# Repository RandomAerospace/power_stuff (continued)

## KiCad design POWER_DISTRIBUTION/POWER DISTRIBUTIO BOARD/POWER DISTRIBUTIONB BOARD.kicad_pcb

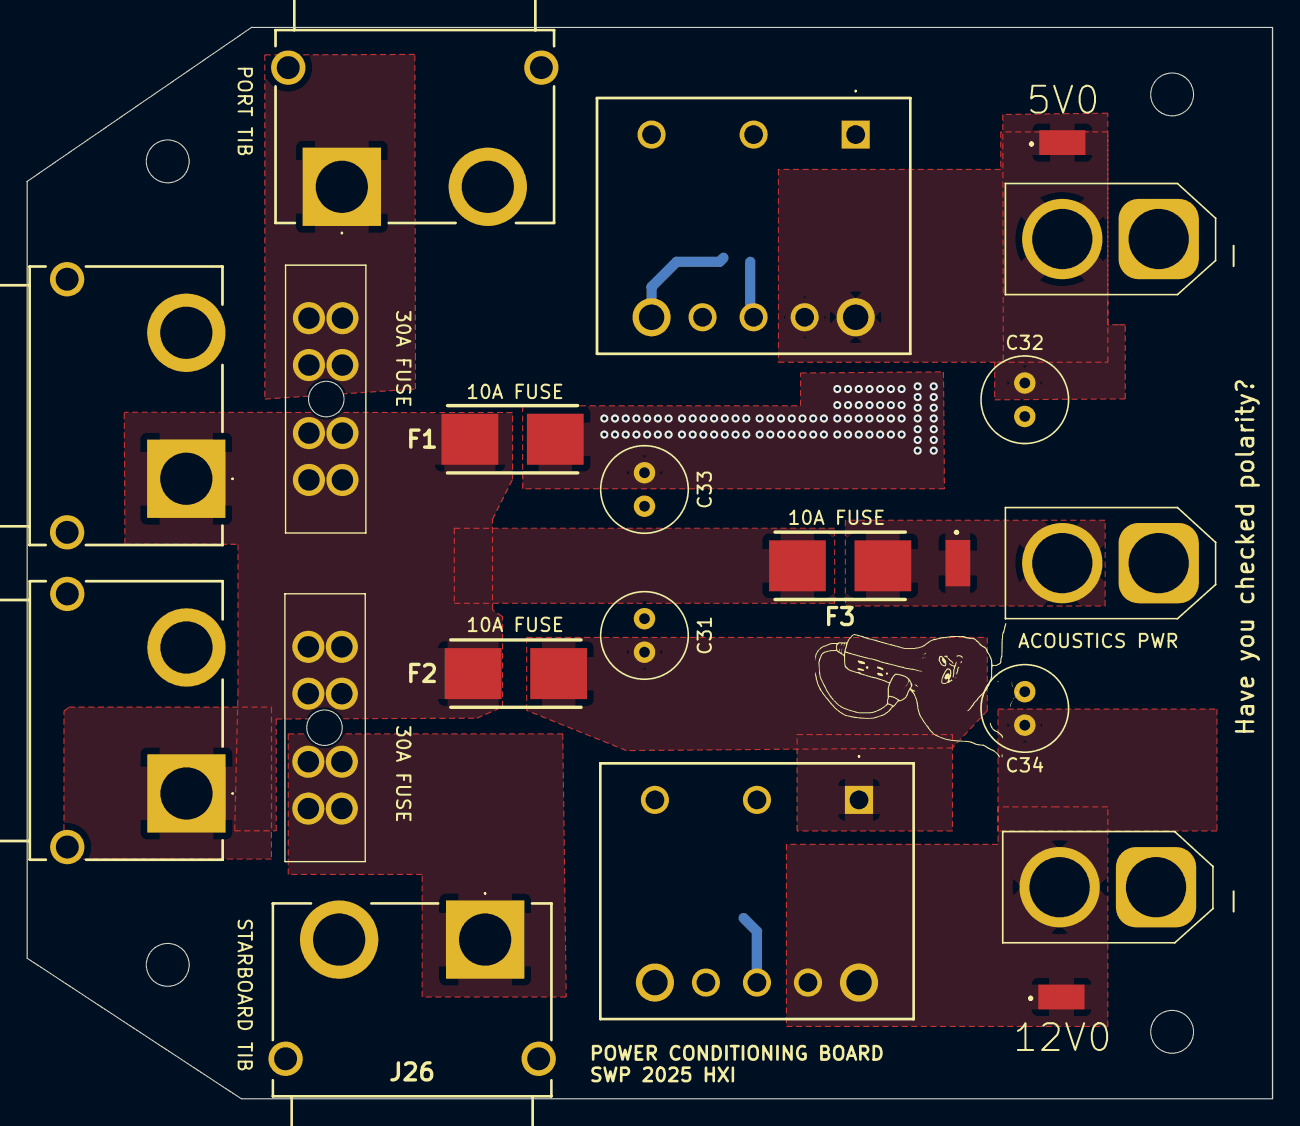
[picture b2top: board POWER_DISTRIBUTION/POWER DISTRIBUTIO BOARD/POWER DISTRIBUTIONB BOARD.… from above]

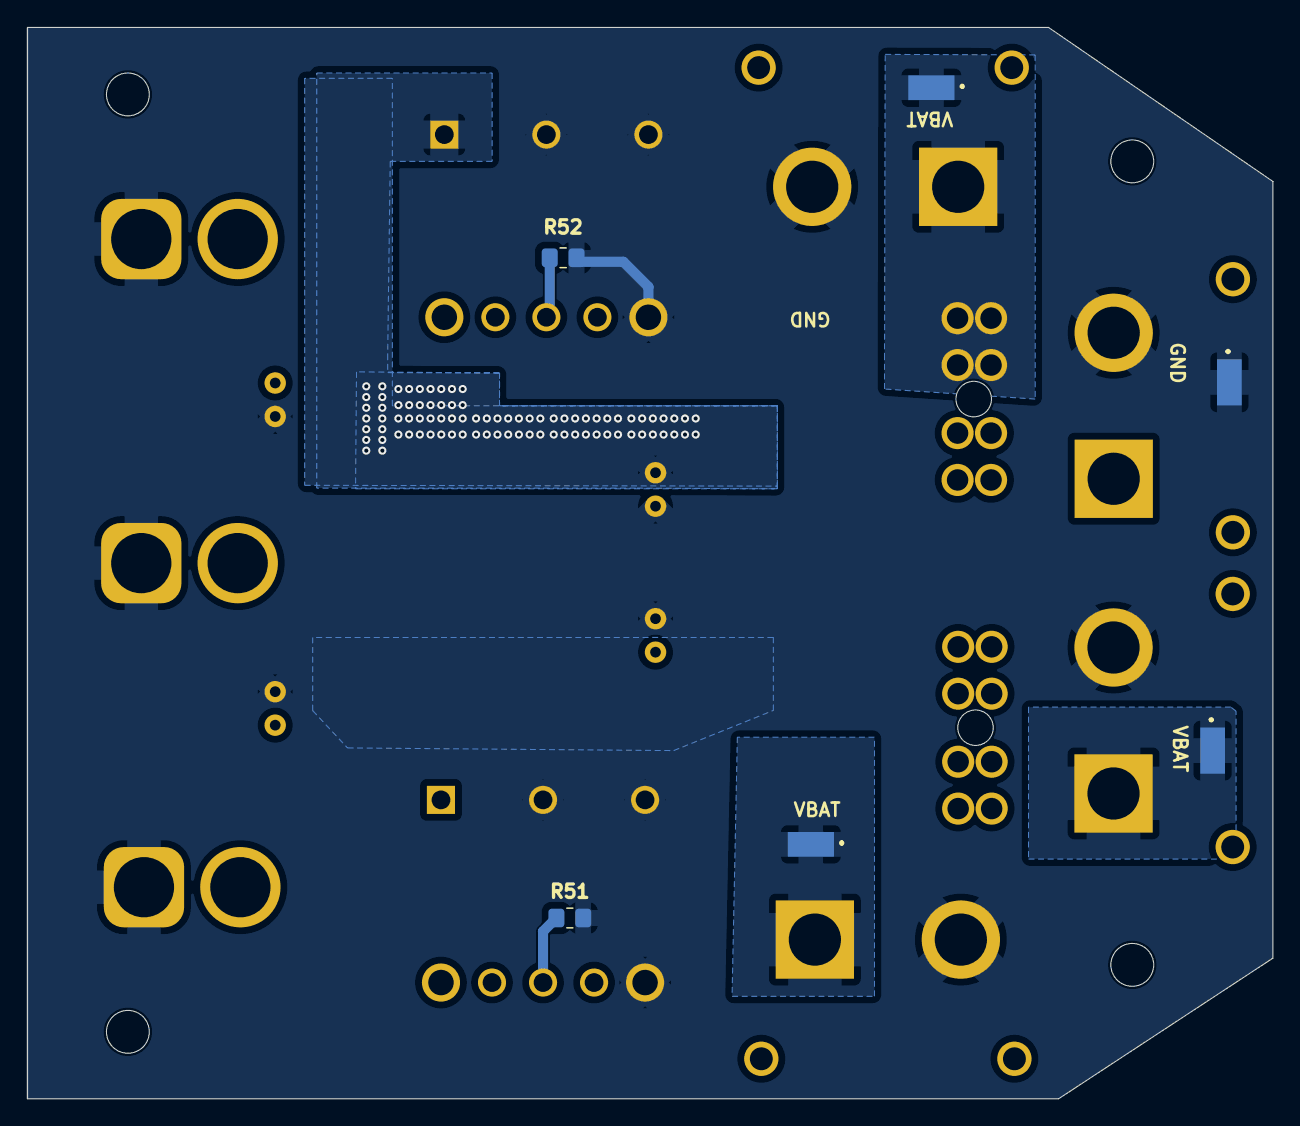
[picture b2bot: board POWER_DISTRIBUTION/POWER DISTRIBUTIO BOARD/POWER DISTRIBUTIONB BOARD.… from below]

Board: 2 copper layers, 93.0 x 80.0 mm, 31 parts (6 on the bottom side), 9 nets.

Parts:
C31, C32, C33, C34: 47u; C_Radial_D6.3mm_H5.0mm_P2.50mm
F1, F2, F3: 0154010.DR; 0154001.DRT
H1, H2, H3, H4: MountingHole; MountingHole_3.2mm_M3_ISO7380
J1, J4, J7: Conn_01x02_Socket; AMASS_XT60-F_1x02_P7.20mm_Vertical
J25, J26, J27, J28: XT90PW-F; XT90PWF
PS3, PS4: RPMA5.0-8.0_OF; RPMA5080OF
R51: 1k82; R_0805_2012Metric_Pad1.20x1.40mm_HandSolder
R52: 8k66; R_0805_2012Metric_Pad1.20x1.40mm_HandSolder
TP3, TP4, TP5, TP6, TP7, TP8, TP24: S1751-46R; S175146R
U2, U3: 178.6165.0002; 17861650002

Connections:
+5V: C32.1, J7.2, PS4.7 (+SENSE), PS4.8 (+VOUT), TP5.1
+12V: C34.1, J1.2, PS3.7 (+SENSE), PS3.8 (+VOUT), TP3.1
GND: C31.2, C32.2, C33.2, C34.2, J1.1, J4.1, J7.1, J25.2 (-), J26.2 (-), J27.2 (-), J28.2 (-), PS3.2 (CTRL), PS3.3 (-VIN), PS3.4 (-VOUT), PS4.2 (CTRL), PS4.3 (-VIN), PS4.4 (-VOUT), R51.2, R52.2, TP7.1
unnamed: PS3.6 (TRIM), R51.1
unnamed: PS4.6 (TRIM), R52.1
VBAT+: C31.1, C33.1, F1.1, F1.2, F2.1, F2.2, F3.1, J27.1 (+), J28.1 (+), PS3.1 (+VIN), PS4.1 (+VIN), TP6.1, U2.5, U2.6, U2.7, U2.8, U3.5, U3.6, U3.7, U3.8
VBAT_A_FUSED: F3.2, J4.2, TP4.1
VBAT_FUSED: J26.1 (+), TP8.1, U3.1, U3.2, U3.3, U3.4
VBAT_P_FUSED: J25.1 (+), TP24.1, U2.1, U2.2, U2.3, U2.4

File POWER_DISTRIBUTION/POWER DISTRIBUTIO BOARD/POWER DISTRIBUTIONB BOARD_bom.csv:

"Id";"Designator";"Footprint";"Quantity";"Designation";"Supplier and ref";
1;"TP4,TP5,TP3,TP6,TP8,TP24,TP7";"S175146R";7;"S1751-46R";;;
2;"F2,F1,F3";"0154001.DRT";3;"0154010.DR";;;
3;"C31,C34,C33,C32";"C_Radial_D6.3mm_H5.0mm_P2.50mm";4;"47u";;;
4;"J25,J26,J28,J27";"XT90PWF";4;"XT90PW-F";;;
5;"J7,J4,J1";"AMASS_XT60-F_1x02_P7.20mm_Vertical";3;"Conn_01x02_Socket";;;
6;"PS3,PS4";"RPMA5080OF";2;"RPMA5.0-8.0_OF";;;
7;"U3,U2";"17861650002";2;"178.6165.0002";;;
8;"R52";"R_0805_2012Metric_Pad1.20x1.40mm_HandSolder";1;"8k66";;;
9;"R51";"R_0805_2012Metric_Pad1.20x1.40mm_HandSolder";1;"1k82";;;

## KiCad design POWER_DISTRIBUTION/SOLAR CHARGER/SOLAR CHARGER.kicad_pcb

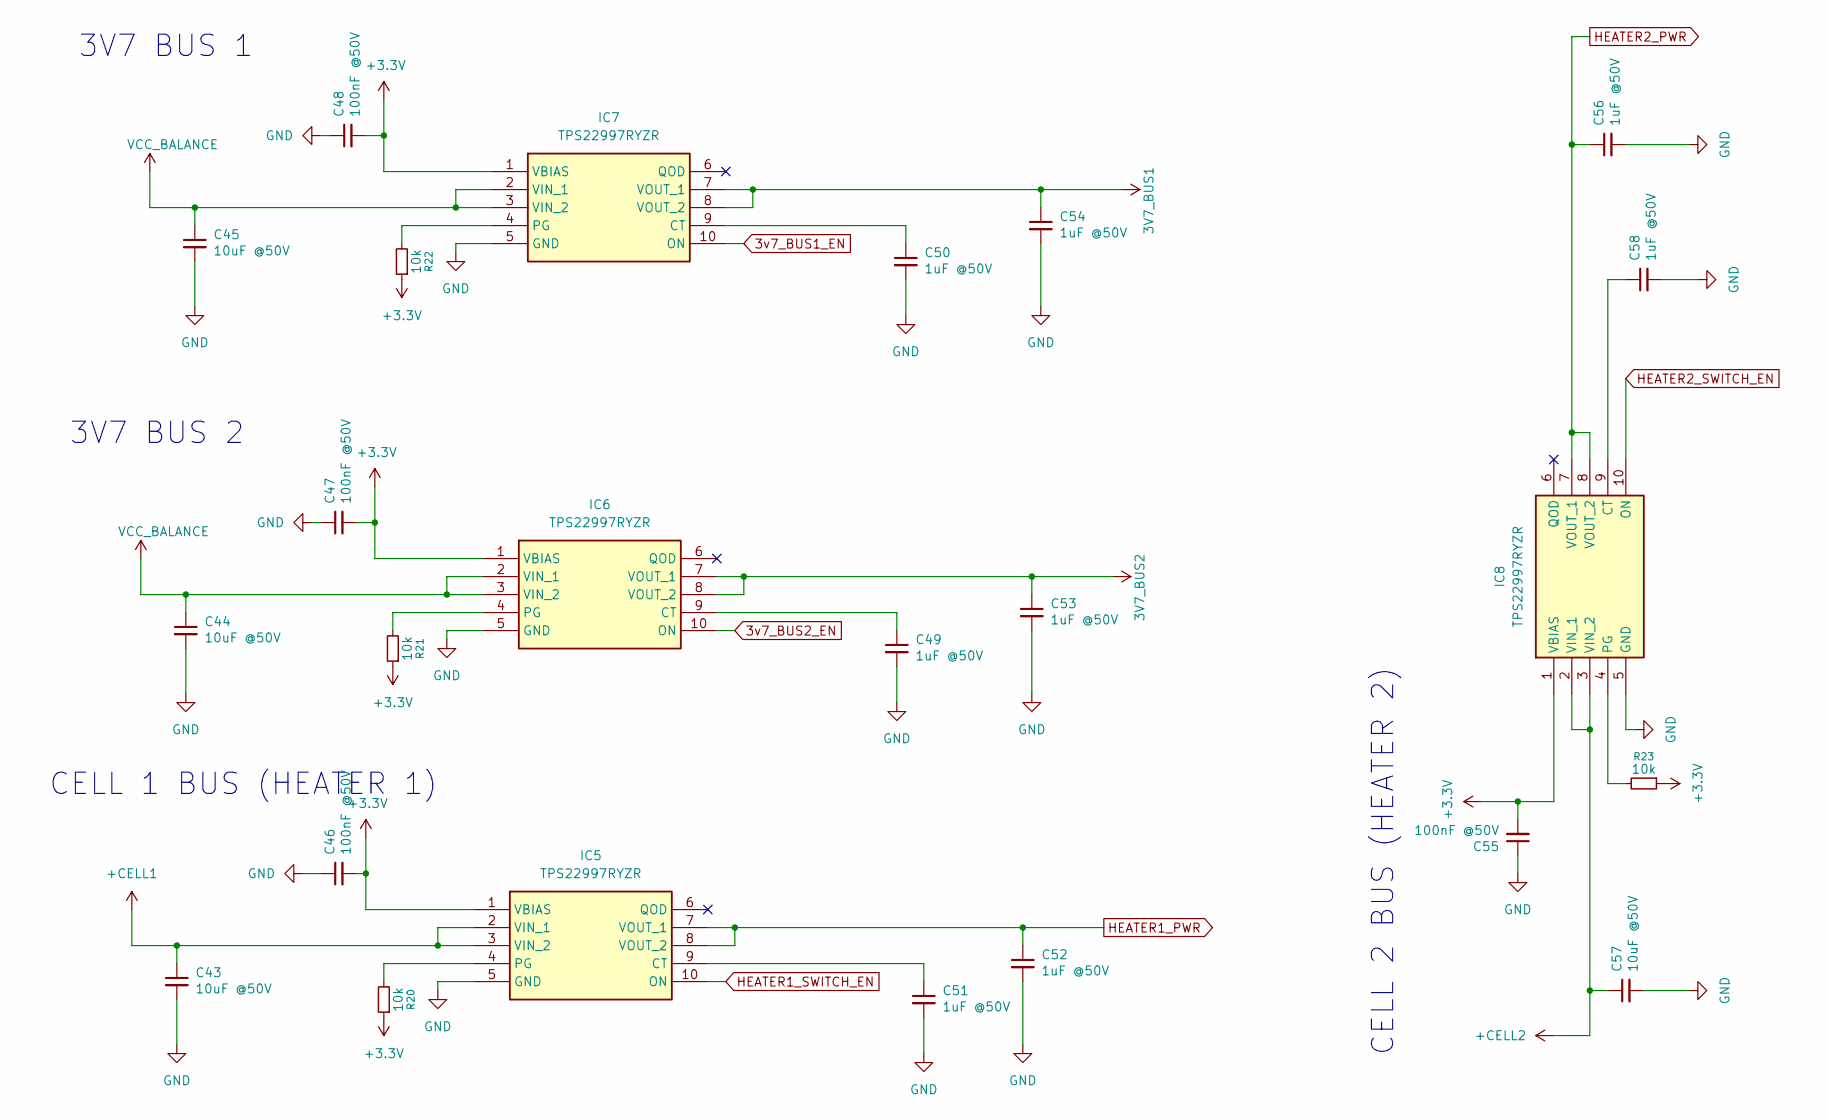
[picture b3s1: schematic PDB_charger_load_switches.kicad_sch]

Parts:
C43, C44, C45, C57: 10uF @50V; C_1210_3225Metric_Pad1.33x2.70mm_HandSolder
C46, C47, C48, C55: 100nF @50V; C_0402_1005Metric_Pad0.74x0.62mm_HandSolder
C49, C50, C51, C52, C53, C54, C56, C58: 1uF @50V; C_0805_2012Metric_Pad1.18x1.45mm_HandSolder
IC5, IC6, IC7, IC8: TPS22997RYZR; Mouser Part Number 595-TPS22997RYZR
R20, R21, R22, R23: 10k; R_0402_1005Metric_Pad0.72x0.64mm_HandSolder

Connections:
3V7_BUS1: C54.1, IC7.7 (VOUT_1), IC7.8 (VOUT_2); also elsewhere on the board
3V7_BUS2: C53.1, IC6.7 (VOUT_1), IC6.8 (VOUT_2); also elsewhere on the board
3v7_BUS1_EN: IC7.10 (ON); also elsewhere on the board
3v7_BUS2_EN: IC6.10 (ON); also elsewhere on the board
+3.3V: C46.2, C47.2, C48.2, C55.2, IC5.1 (VBIAS), IC6.1 (VBIAS), IC7.1 (VBIAS), IC8.1 (VBIAS), R20.1, R21.1, R22.1, R23.1; also elsewhere on the board
+CELL1: C43.1, IC5.2 (VIN_1), IC5.3 (VIN_2); also elsewhere on the board
+CELL2: C57.1, IC8.2 (VIN_1), IC8.3 (VIN_2); also elsewhere on the board
GND: C43.2, C44.2, C45.2, C46.1, C47.1, C48.1, C49.2, C50.2, C51.2, C52.2, C53.2, C54.2, C55.1, C56.2, C57.2, C58.2, IC5.5 (GND), IC6.5 (GND), IC7.5 (GND), IC8.5 (GND); also elsewhere on the board
HEATER1_PWR: C52.1, IC5.7 (VOUT_1), IC5.8 (VOUT_2); also elsewhere on the board
HEATER1_SWITCH_EN: IC5.10 (ON); also elsewhere on the board
HEATER2_PWR: C56.1, IC8.7 (VOUT_1), IC8.8 (VOUT_2); also elsewhere on the board
HEATER2_SWITCH_EN: IC8.10 (ON); also elsewhere on the board
unnamed: C51.1, IC5.9 (CT)
unnamed: IC5.4 (PG), R20.2
unnamed: C49.1, IC6.9 (CT)
unnamed: IC6.4 (PG), R21.2
unnamed: C50.1, IC7.9 (CT)
unnamed: IC7.4 (PG), R22.2
unnamed: C58.1, IC8.9 (CT)
unnamed: IC8.4 (PG), R23.2
VCC_BALANCE: C44.1, C45.1, IC6.2 (VIN_1), IC6.3 (VIN_2), IC7.2 (VIN_1), IC7.3 (VIN_2); also elsewhere on the board

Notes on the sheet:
3V7 BUS 2
CELL 2 BUS (HEATER 2)
CELL 1 BUS (HEATER 1)
3V7 BUS 1

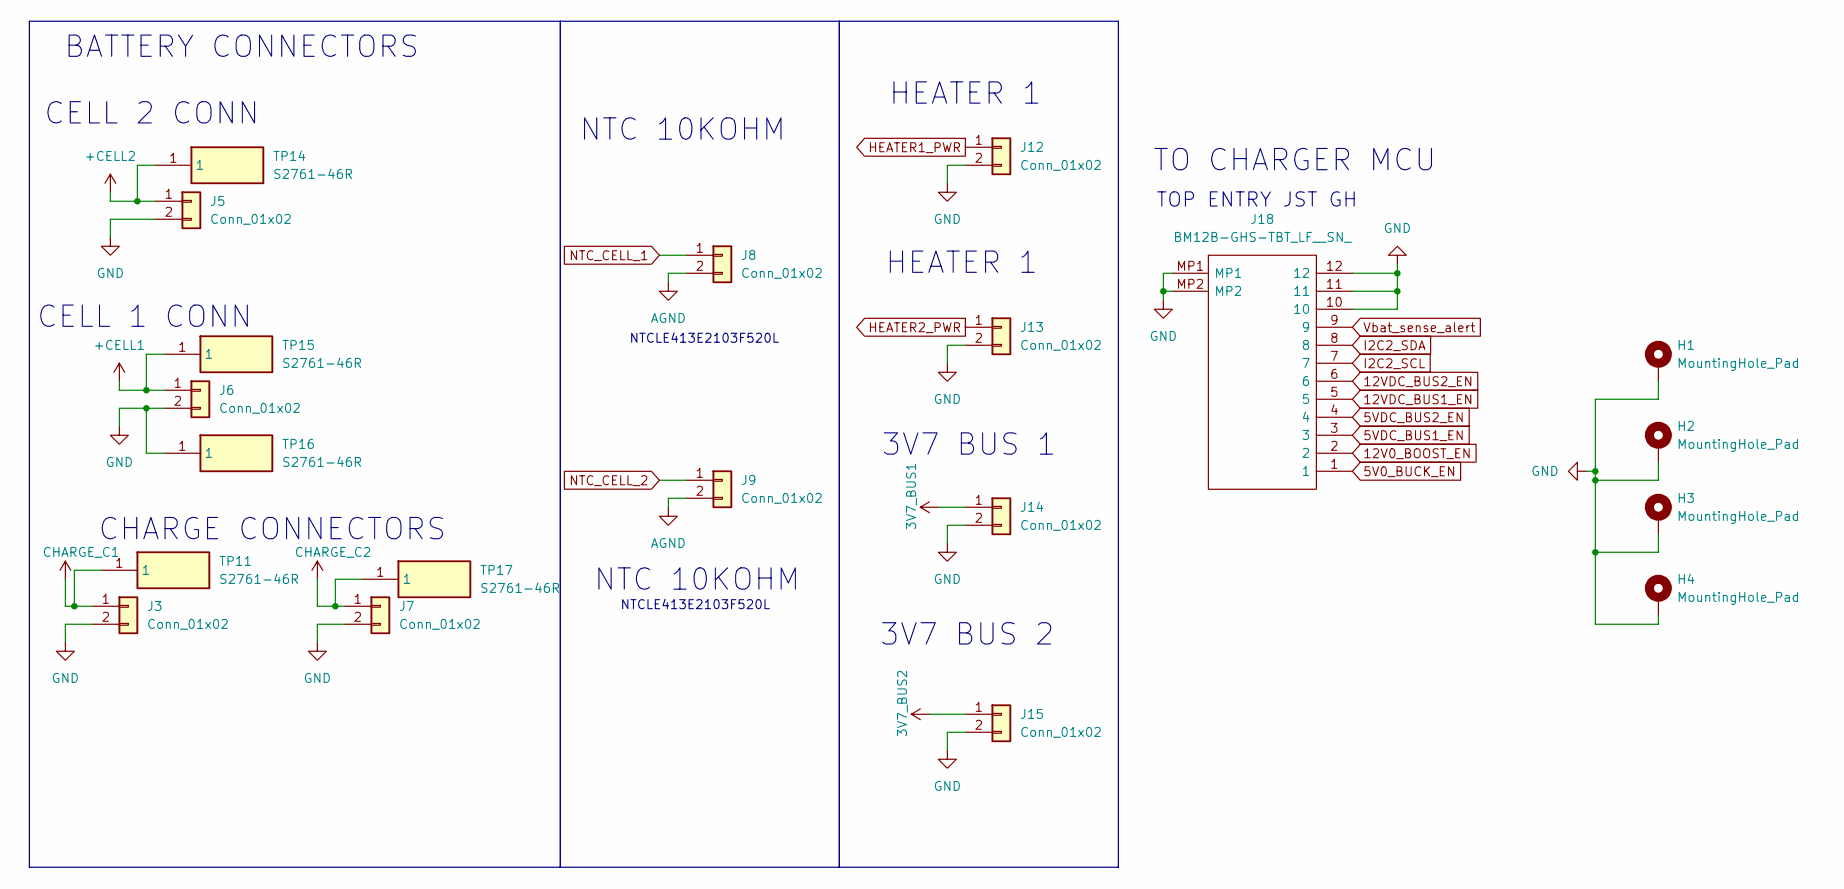
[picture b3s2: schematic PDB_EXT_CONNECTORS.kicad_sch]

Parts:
H1, H2, H3, H4: MountingHole_Pad; MountingHole_3.2mm_M3_Pad_Via
J3, J5, J6, J7: Conn_01x02; JST_PH_S2B-PH-K_1x02_P2.00mm_Horizontal
J8, J9: Conn_01x02; SolderWire-0.127sqmm_1x02_P3.7mm_D0.48mm_OD1mm
J12, J13, J14, J15: Conn_01x02; JST_PH_B2B-PH-K_1x02_P2.00mm_Vertical
J18: BM12B-GHS-TBT_LF__SN_; BM12BGHSTBTLFSN; Mouser Part Number 306-BM12BGHSTBTLFSNN
TP11, TP14, TP15, TP16, TP17: S2761-46R; S276146R; Mouser Part Number 855-S2761-46R

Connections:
3V7_BUS1: J14.1; also elsewhere on the board
3V7_BUS2: J15.1; also elsewhere on the board
5V0_BUCK_EN: J18.1; also elsewhere on the board
5VDC_BUS1_EN: J18.3; also elsewhere on the board
5VDC_BUS2_EN: J18.4; also elsewhere on the board
12V0_BOOST_EN: J18.2; also elsewhere on the board
12VDC_BUS1_EN: J18.5; also elsewhere on the board
12VDC_BUS2_EN: J18.6; also elsewhere on the board
+CELL1: J6.1, TP15.1; also elsewhere on the board
+CELL2: J5.1, TP14.1; also elsewhere on the board
AGND: J8.2, J9.2
CHARGE_C1: J3.1, TP11.1; also elsewhere on the board
CHARGE_C2: J7.1, TP17.1; also elsewhere on the board
GND: H1.1, H2.1, H3.1, H4.1, J3.2, J5.2, J6.2, J7.2, J12.2, J13.2, J14.2, J15.2, J18.10, J18.11, J18.12, J18.MP1, J18.MP2, TP16.1; also elsewhere on the board
HEATER1_PWR: J12.1; also elsewhere on the board
HEATER2_PWR: J13.1; also elsewhere on the board
I2C2_SCL: J18.7; also elsewhere on the board
I2C2_SDA: J18.8; also elsewhere on the board
NTC_CELL_1: J8.1; also elsewhere on the board
NTC_CELL_2: J9.1; also elsewhere on the board
Vbat_sense_alert: J18.9; also elsewhere on the board

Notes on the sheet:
TO CHARGER MCU
HEATER 1
TOP ENTRY JST GH
CELL 2 CONN
3V7 BUS 1
NTC 10KOHM
NTCLE413E2103F520L
CELL 1 CONN
BATTERY CONNECTORS
3V7 BUS 2
CHARGE CONNECTORS

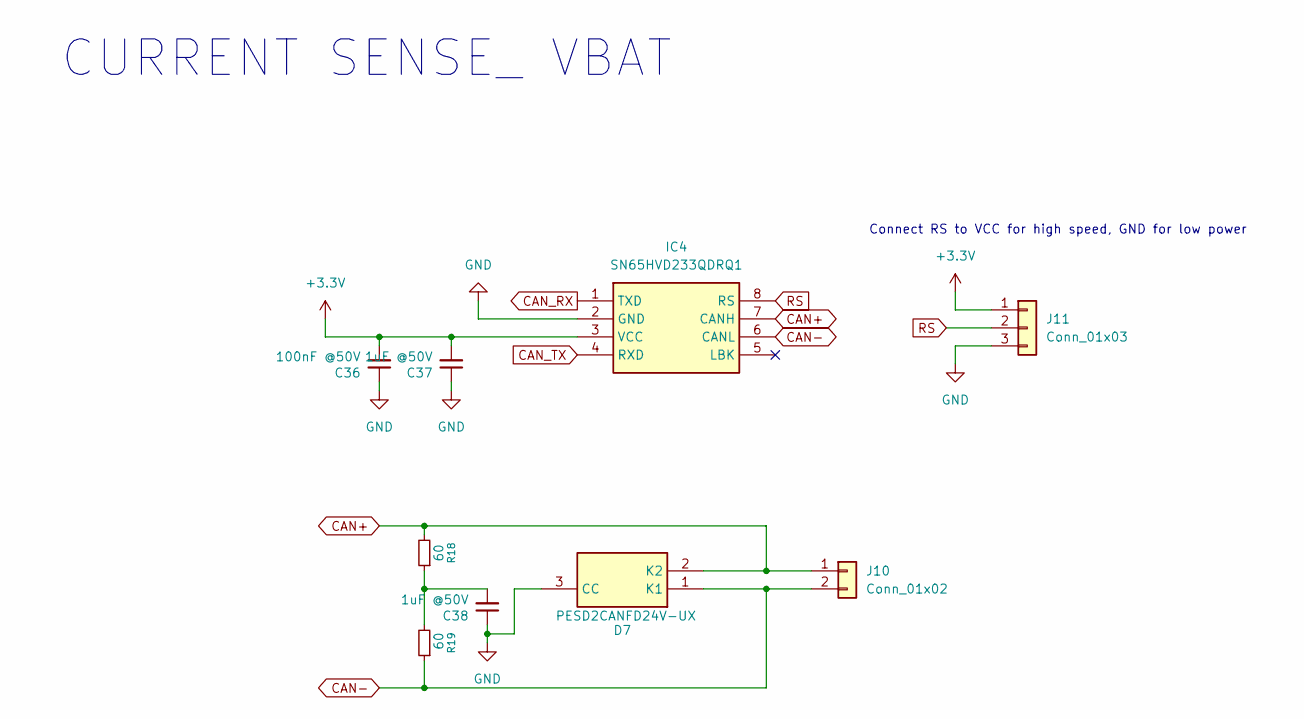
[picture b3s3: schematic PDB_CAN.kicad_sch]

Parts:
C36: 100nF @50V; C_0402_1005Metric_Pad0.74x0.62mm_HandSolder
C37, C38: 1uF @50V; C_0805_2012Metric_Pad1.18x1.45mm_HandSolder
D7: PESD2CANFD24V-UX; SOT65P210X110-3N; Mouser Part Number 771-PESD2CANFD24V-UX
IC4: SN65HVD233QDRQ1; SOIC127P600X175-8N; Mouser Part Number 595-SN65HVD233QDRQ1
J10: Conn_01x02; JST_PH_B2B-PH-K_1x02_P2.00mm_Vertical
J11: Conn_01x03; PinHeader_1x03_P2.54mm_Vertical
R18, R19: 60; R_0603_1608Metric

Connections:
+3.3V: C36.2, C37.2, IC4.3 (VCC), J11.1; also elsewhere on the board
CAN+: D7.2 (K2), IC4.7 (CANH), J10.1, R18.2
CAN-: D7.1 (K1), IC4.6 (CANL), J10.2, R19.1
CAN_RX: IC4.1 (TXD); also elsewhere on the board
CAN_TX: IC4.4 (RXD); also elsewhere on the board
GND: C36.1, C37.1, C38.1, D7.3 (CC), IC4.2 (GND), J11.3; also elsewhere on the board
unnamed: C38.2, R18.1, R19.2
RS: IC4.8 (RS), J11.2

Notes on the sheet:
Connect RS to VCC for high speed, GND for low power
CURRENT SENSE_ VBAT

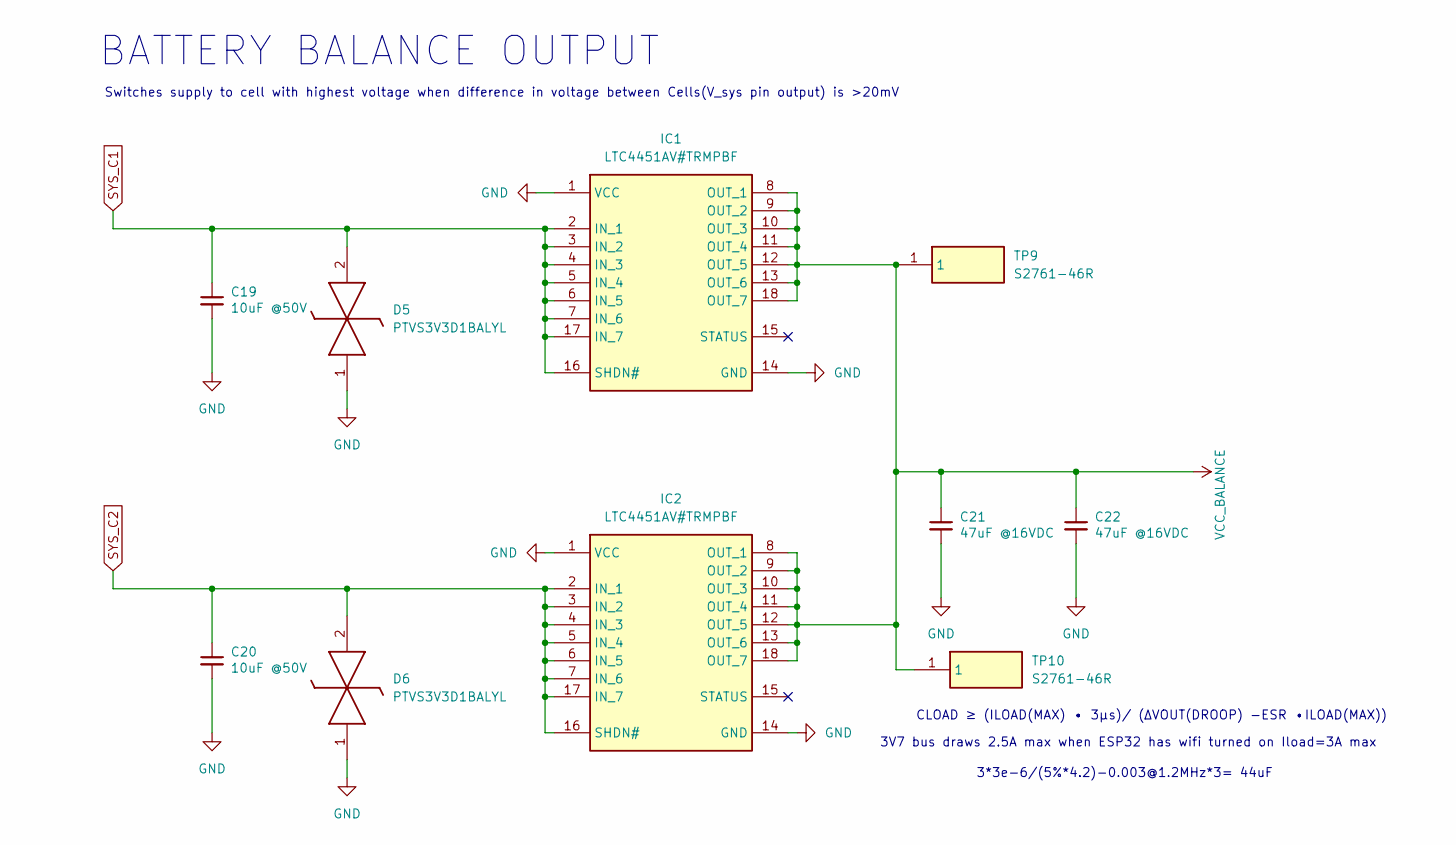
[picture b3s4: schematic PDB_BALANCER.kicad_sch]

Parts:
C19, C20: 10uF @50V; C_1210_3225Metric_Pad1.33x2.70mm_HandSolder
C21, C22: 47uF @16VDC; C_1206_3216Metric_Pad1.33x1.80mm_HandSolder
D5, D6: PTVS3V3D1BALYL; PESD5V0S1BL315; Mouser Part Number 771-PTVS3V3D1BALYL
IC1, IC2: LTC4451AV#TRMPBF; LTC4451AVTRMPBF; Mouser Part Number 584-LTC4451AVTRMPBF
TP9, TP10: S2761-46R; S276146R; Mouser Part Number 855-S2761-46R

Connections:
GND: C19.2, C20.2, C21.2, C22.2, D5.1 (K1), D6.1 (K1), IC1.1 (VCC), IC1.14 (GND), IC2.1 (VCC), IC2.14 (GND); also elsewhere on the board
SYS_C1: C19.1, D5.2 (K2), IC1.2 (IN_1), IC1.3 (IN_2), IC1.4 (IN_3), IC1.5 (IN_4), IC1.6 (IN_5), IC1.7 (IN_6), IC1.16 (SHDN#), IC1.17 (IN_7); also elsewhere on the board
SYS_C2: C20.1, D6.2 (K2), IC2.2 (IN_1), IC2.3 (IN_2), IC2.4 (IN_3), IC2.5 (IN_4), IC2.6 (IN_5), IC2.7 (IN_6), IC2.16 (SHDN#), IC2.17 (IN_7); also elsewhere on the board
VCC_BALANCE: C21.1, C22.1, IC1.8 (OUT_1), IC1.9 (OUT_2), IC1.10 (OUT_3), IC1.11 (OUT_4), IC1.12 (OUT_5), IC1.13 (OUT_6), IC1.18 (OUT_7), IC2.8 (OUT_1), IC2.9 (OUT_2), IC2.10 (OUT_3), IC2.11 (OUT_4), IC2.12 (OUT_5), IC2.13 (OUT_6), IC2.18 (OUT_7), TP9.1, TP10.1; also elsewhere on the board

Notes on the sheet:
BATTERY BALANCE OUTPUT
3*3e-6/(5%*4.2)-0.003@1.2MHz*3= 44uF
Switches supply to cell with highest voltage when difference in voltage between Cells(V_sys pin output) is >20mV
3V7 bus draws 2.5A max when ESP32 has wifi turned on Iload=3A max
CLOAD ≥ (ILOAD(MAX) • 3μs)/ (ΔVOUT(DROOP) -ESR •ILOAD(MAX))

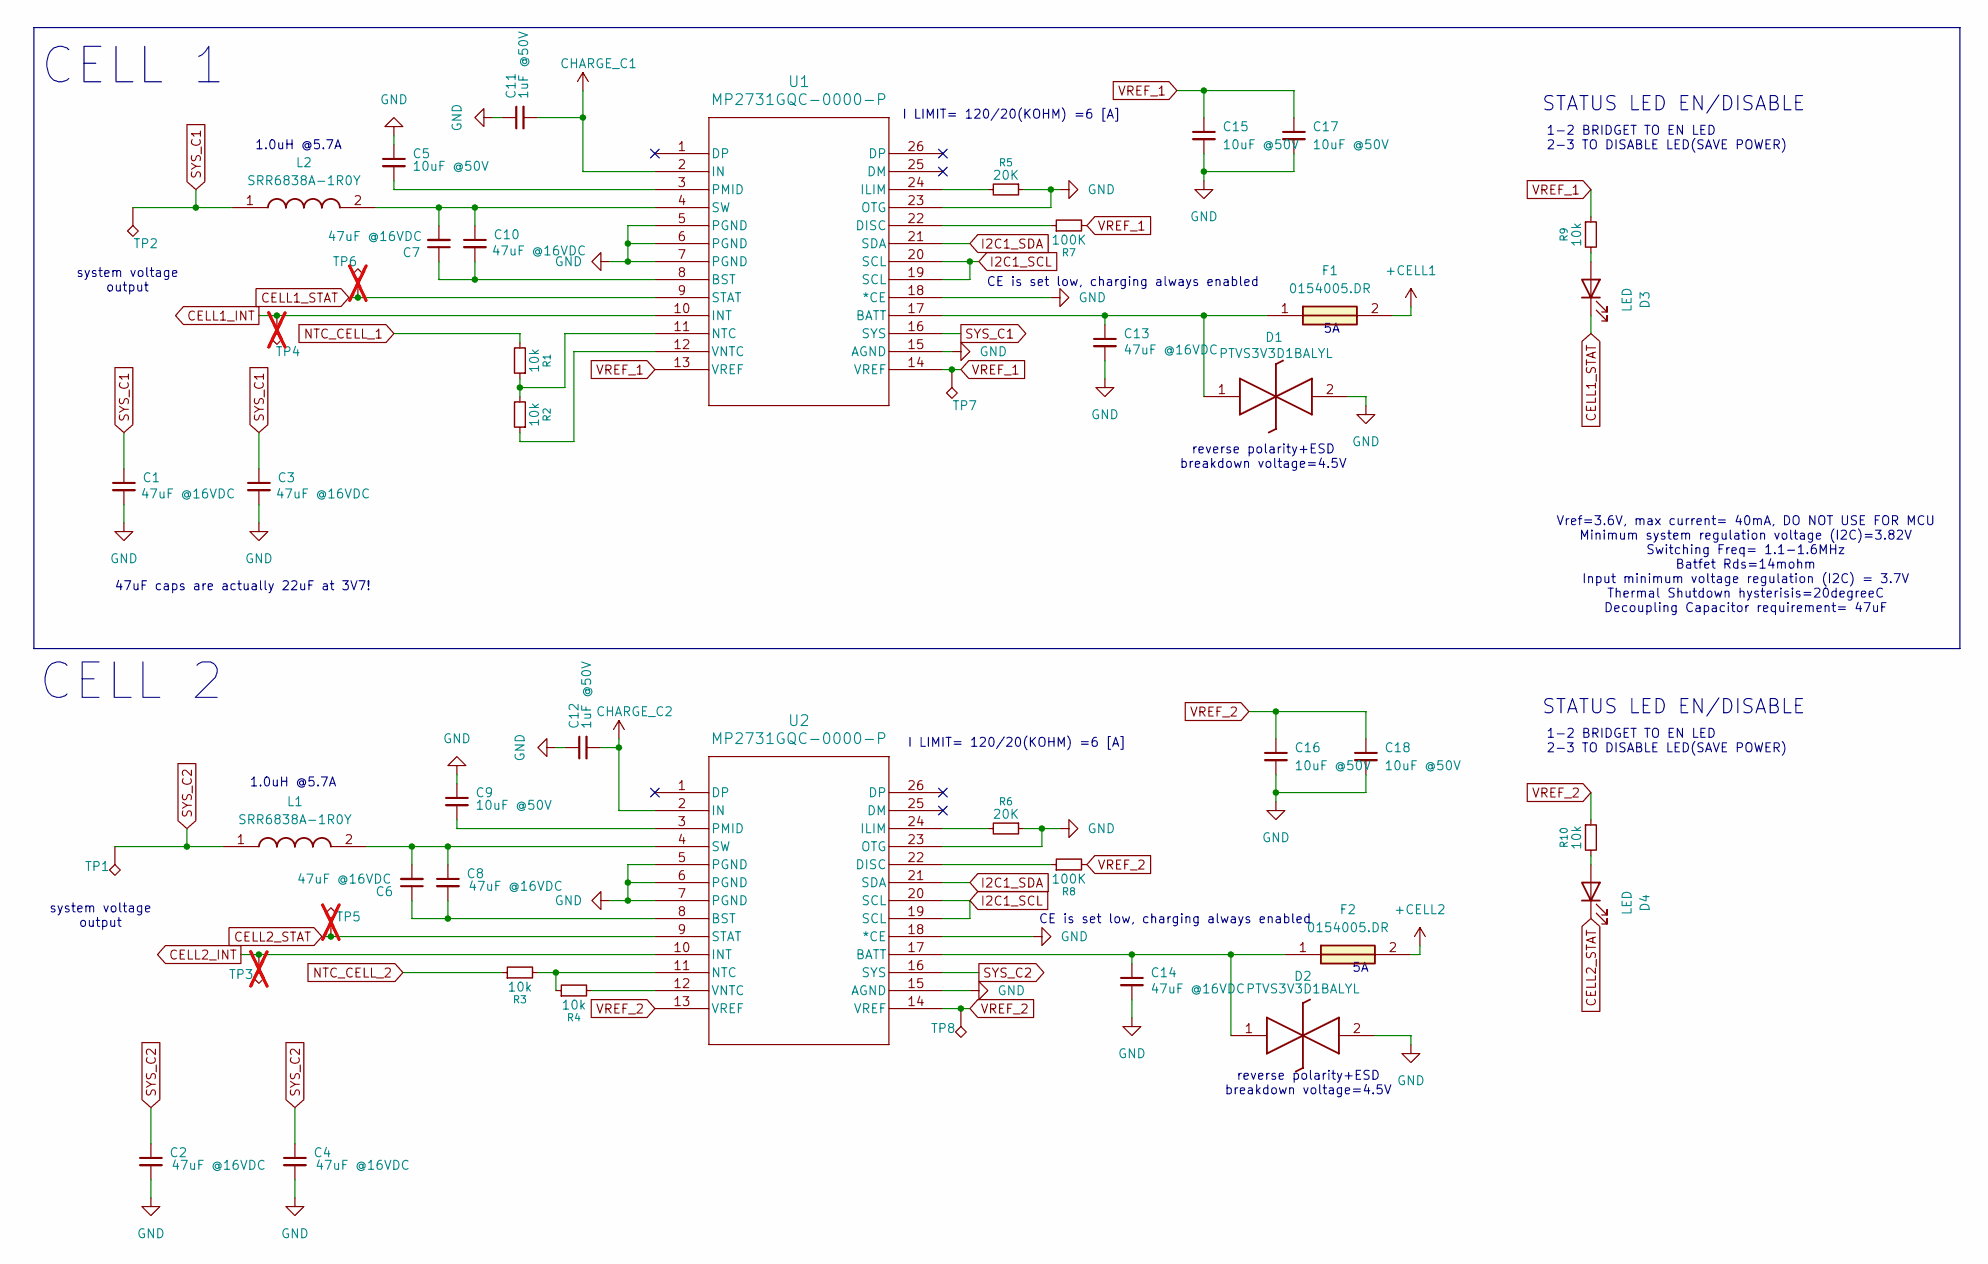
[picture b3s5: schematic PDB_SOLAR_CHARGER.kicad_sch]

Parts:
C1, C2, C3, C4, C6, C7, C8, C10, C13, C14: 47uF @16VDC; C_1206_3216Metric_Pad1.33x1.80mm_HandSolder
C5, C9, C15, C16, C17, C18: 10uF @50V; C_1210_3225Metric_Pad1.33x2.70mm_HandSolder
C11, C12: 1uF @50V; C_0805_2012Metric_Pad1.18x1.45mm_HandSolder
D1, D2: PTVS3V3D1BALYL; PESD5V0S1BL315; Mouser Part Number 771-PTVS3V3D1BALYL
D3, D4: LED; LED_0603_1608Metric_Pad1.05x0.95mm_HandSolder
F1, F2: 0154005.DR; 0154005DR; Mouser Part Number 576-0154005.DR
L1, L2: SRR6838A-1R0Y; INDPM6868X420N; Manufacturer_Part_Number SRR6838A-1R0Y
R1, R2, R3, R4, R9, R10: 10k; R_0402_1005Metric_Pad0.72x0.64mm_HandSolder
R5, R6: 20K; R_0603_1608Metric
R7, R8: 100K; R_0603_1608Metric
TP1, TP2, TP7, TP8: TestPoint_Alt; TestPoint_THTPad_1.0x1.0mm_Drill0.5mm
TP3, TP4, TP5, TP6: TestPoint_Alt; TestPoint_THTPad_1.0x1.0mm_Drill0.5mm; not fitted
U1, U2: MP2731GQC-0000-P; QFN-26_MP2731

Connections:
+CELL1: F1.2; also elsewhere on the board
+CELL2: F2.2; also elsewhere on the board
CELL1_INT: TP4.1, U1.10 (INT); also elsewhere on the board
CELL1_STAT: D3.1 (K), TP6.1, U1.9 (STAT); also elsewhere on the board
CELL2_INT: TP3.1, U2.10 (INT); also elsewhere on the board
CELL2_STAT: D4.1 (K), TP5.1, U2.9 (STAT); also elsewhere on the board
CHARGE_C1: C11.2, U1.2 (IN); also elsewhere on the board
CHARGE_C2: C12.2, U2.2 (IN); also elsewhere on the board
GND: C1.2, C2.2, C3.2, C4.2, C5.1, C9.1, C11.1, C12.1, C13.2, C14.2, C15.2, C16.2, C17.2, C18.2, D1.2 (K2), D2.2 (K2), R5.1, R6.1, U1.5 (PGND), U1.6 (PGND), U1.7 (PGND), U1.15 (AGND), U1.18 (*CE), U1.23 (OTG), U2.5 (PGND), U2.6 (PGND), U2.7 (PGND), U2.15 (AGND), U2.18 (*CE), U2.23 (OTG); also elsewhere on the board
I2C1_SCL: U1.19 (SCL), U1.20 (SCL), U2.19 (SCL), U2.20 (SCL); also elsewhere on the board
I2C1_SDA: U1.21 (SDA), U2.21 (SDA); also elsewhere on the board
NTC_CELL_1: R1.2; also elsewhere on the board
NTC_CELL_2: R3.1; also elsewhere on the board
unnamed: C13.1, D1.1 (K1), F1.1, U1.17 (BATT)
unnamed: C14.1, D2.1 (K1), F2.1, U2.17 (BATT)
unnamed: D3.2 (A), R9.2
unnamed: D4.2 (A), R10.2
unnamed: C7.1, C10.2, U1.8 (BST)
unnamed: R7.1, U1.22 (DISC)
unnamed: R5.2, U1.24 (ILIM)
unnamed: R1.1, R2.2, U1.11 (NTC)
unnamed: C5.2, U1.3 (PMID)
unnamed: C7.2, C10.1, L2.2, U1.4 (SW)
unnamed: R2.1, U1.12 (VNTC)
unnamed: C6.1, C8.2, U2.8 (BST)
unnamed: R8.1, U2.22 (DISC)
unnamed: R6.2, U2.24 (ILIM)
unnamed: R3.2, R4.1, U2.11 (NTC)
unnamed: C9.2, U2.3 (PMID)
unnamed: C6.2, C8.1, L1.2, U2.4 (SW)
unnamed: R4.2, U2.12 (VNTC)
SYS_C1: C1.1, C3.1, L2.1, TP2.1, U1.16 (SYS); also elsewhere on the board
SYS_C2: C2.1, C4.1, L1.1, TP1.1, U2.16 (SYS); also elsewhere on the board
VREF_1: C15.1, C17.1, R7.2, R9.1, TP7.1, U1.13 (VREF), U1.14 (VREF)
VREF_2: C16.1, C18.1, R8.2, R10.1, TP8.1, U2.13 (VREF), U2.14 (VREF)

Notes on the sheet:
reverse polarity+ESD breakdown voltage=4.5V
47uF caps are actually 22uF at 3V7!
I LIMIT= 120/20(KOHM) =6 [A]
CELL 1
1-2 BRIDGET TO EN LED 2-3 TO DISABLE LED(SAVE POWER)
CELL 2
Vref=3.6V, max current= 40mA, DO NOT USE FOR MCU Minimum system regulation voltage (I2C)=3.82V Switching Freq= 1.1-1.6MHz Batfet Rds=14mohm Input minimum voltage regulation (I2C) = 3.7V Thermal Shutdown hysterisis=20degreeC Decoupling Capacitor requirement= 47uF
system voltage output
1.0uH @5.7A
reverse polarity+ESD breakdown voltage=4.5V
STATUS LED EN/DISABLE
CE is set low, charging always enabled

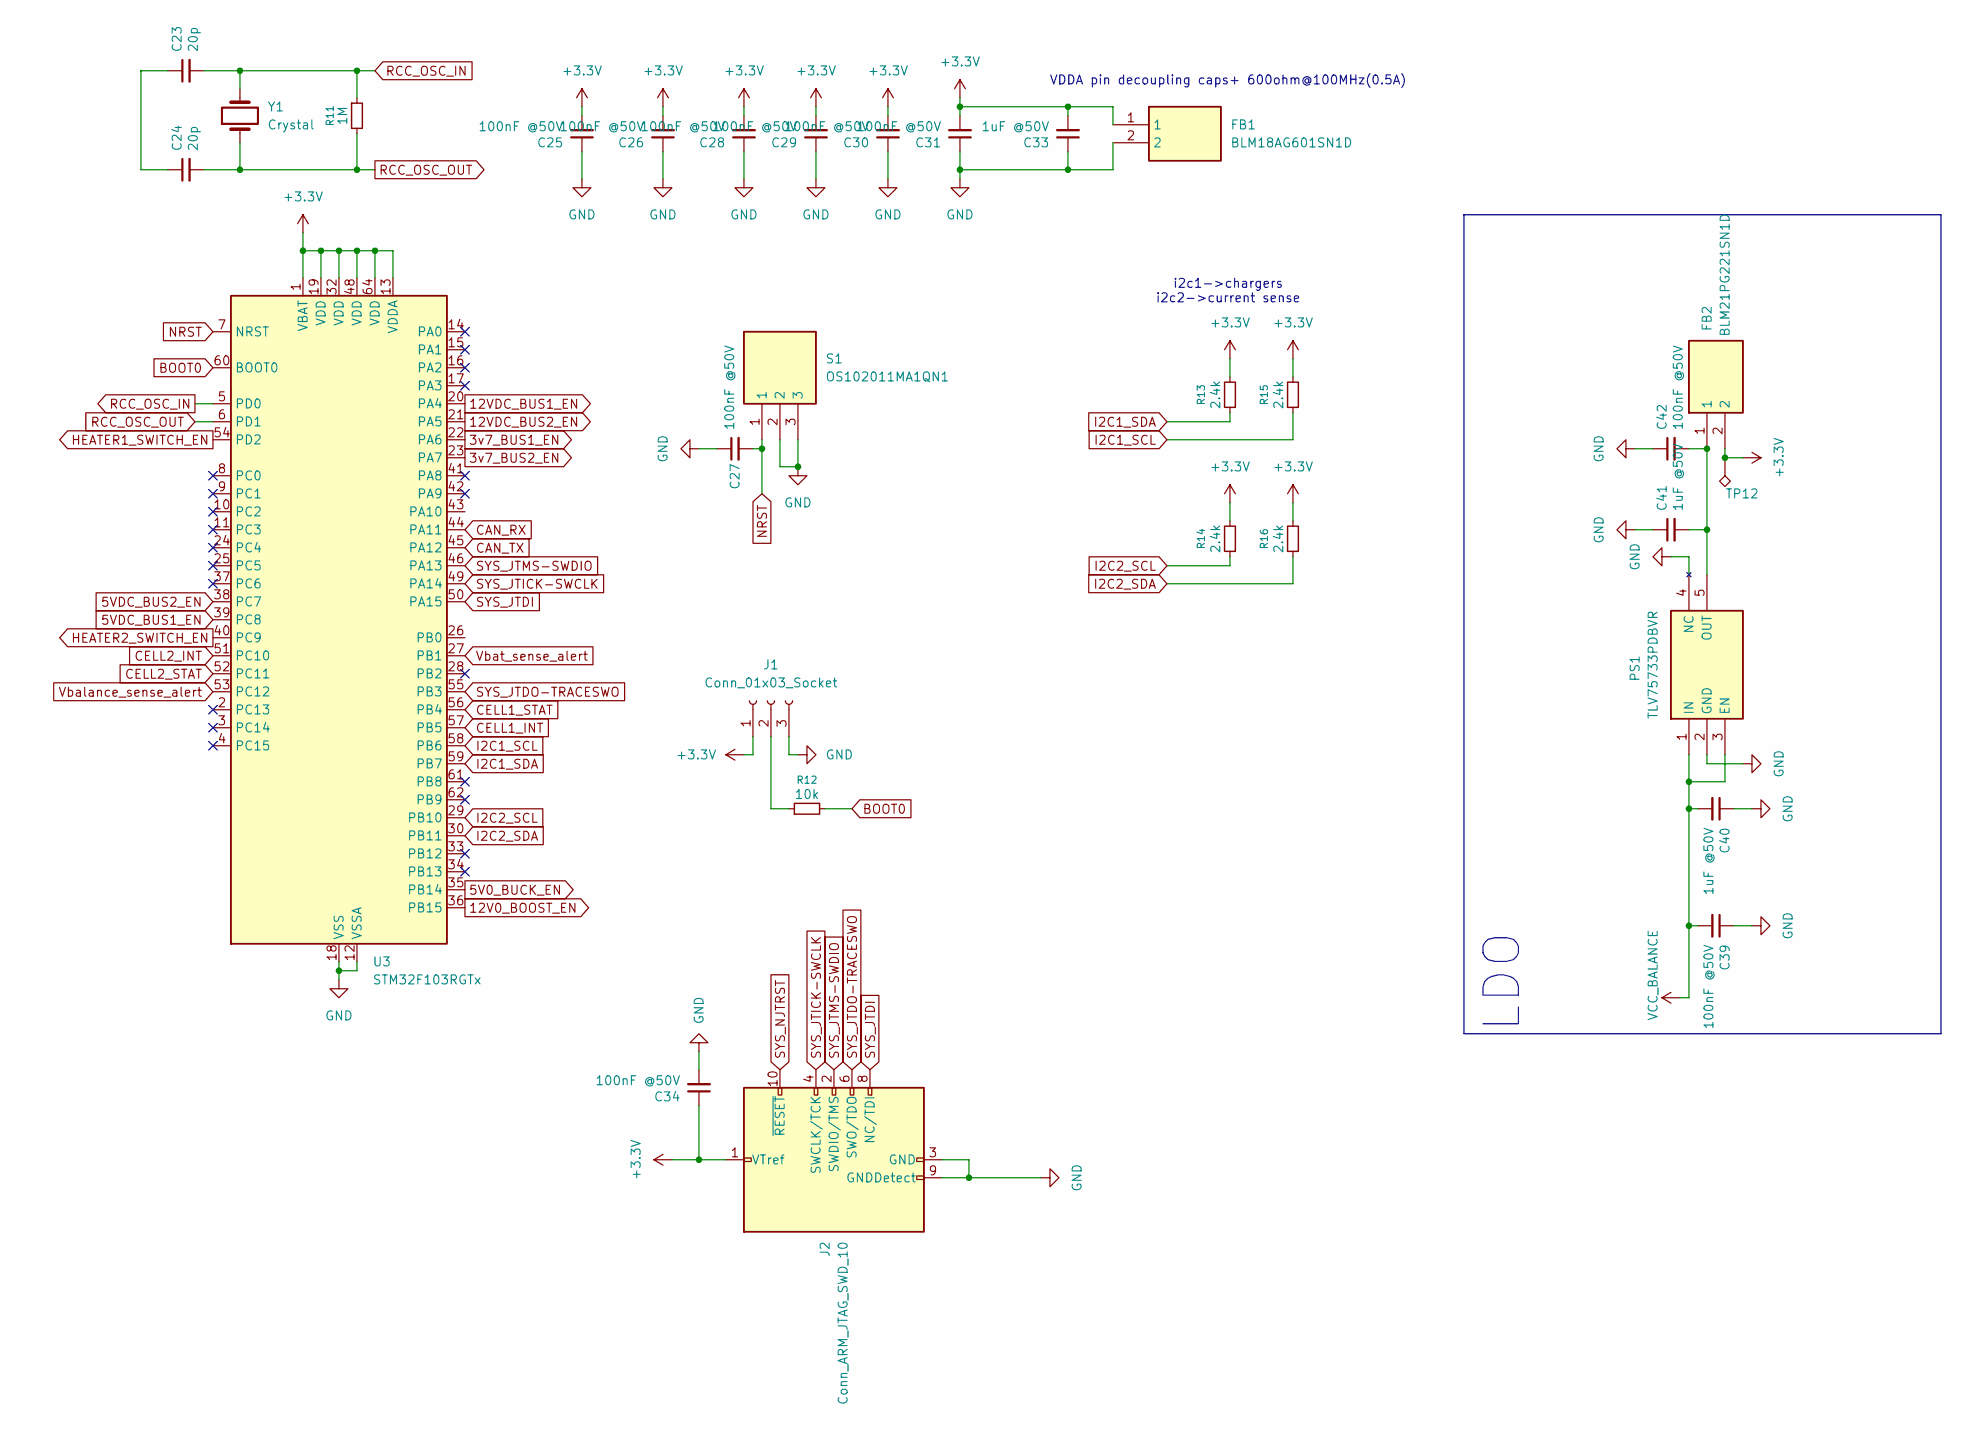
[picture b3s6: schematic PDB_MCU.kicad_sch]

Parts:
C23, C24: 20p; C_0402_1005Metric_Pad0.74x0.62mm_HandSolder
C25, C26, C27, C28, C29, C30, C31, C34, C39, C42: 100nF @50V; C_0402_1005Metric_Pad0.74x0.62mm_HandSolder
C33, C40, C41: 1uF @50V; C_0805_2012Metric_Pad1.18x1.45mm_HandSolder
FB1: BLM18AG601SN1D; BLM18SP221SN1B; Mouser Part Number 81-BLM11A601S
FB2: BLM21PG221SN1D; BEADC2012X105N; Mouser Part Number 81-BLM21P221SG
J1: Conn_01x03_Socket; PinHeader_1x03_P2.54mm_Vertical
J2: Conn_ARM_JTAG_SWD_10; PinHeader_2x05_P1.27mm_Horizontal
PS1: TLV75733PDBVR; SOT95P280X145-5N; Mouser Part Number 595-TLV75733PDBVR
R11: 1M; R_0603_1608Metric
R12: 10k; R_0402_1005Metric_Pad0.72x0.64mm_HandSolder
R13, R14, R15, R16: 2.4k; R_0603_1608Metric
S1: OS102011MA1QN1; Mouser Part Number 611-OS102011MA1QN1
TP12: TestPoint_Alt; TestPoint_THTPad_1.0x1.0mm_Drill0.5mm
U3: STM32F103RGTx; LQFP-64_10x10mm_P0.5mm
Y1: Crystal; Crystal_SMD_5032-2Pin_5.0x3.2mm

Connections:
3v7_BUS1_EN: U3.22 (PA6); also elsewhere on the board
3v7_BUS2_EN: U3.23 (PA7); also elsewhere on the board
5V0_BUCK_EN: U3.35 (PB14); also elsewhere on the board
5VDC_BUS1_EN: U3.39 (PC8); also elsewhere on the board
5VDC_BUS2_EN: U3.38 (PC7); also elsewhere on the board
12V0_BOOST_EN: U3.36 (PB15); also elsewhere on the board
12VDC_BUS1_EN: U3.20 (PA4); also elsewhere on the board
12VDC_BUS2_EN: U3.21 (PA5); also elsewhere on the board
+3.3V: C25.2, C26.2, C28.2, C29.2, C30.2, C31.2, C33.2, C34.1, FB1.1, FB2.2, J1.1, J2.1 (VTref), R13.2, R14.2, R15.2, R16.2, TP12.1, U3.1 (VBAT), U3.13 (VDDA), U3.19 (VDD), U3.32 (VDD), U3.48 (VDD), U3.64 (VDD); also elsewhere on the board
BOOT0: R12.2, U3.60 (BOOT0)
CAN_RX: U3.44 (PA11); also elsewhere on the board
CAN_TX: U3.45 (PA12); also elsewhere on the board
CELL1_INT: U3.57 (PB5); also elsewhere on the board
CELL1_STAT: U3.56 (PB4); also elsewhere on the board
CELL2_INT: U3.51 (PC10); also elsewhere on the board
CELL2_STAT: U3.52 (PC11); also elsewhere on the board
GND: C25.1, C26.1, C27.1, C28.1, C29.1, C30.1, C31.1, C33.1, C34.2, C39.1, C40.1, C41.1, C42.1, FB1.2, J1.3, J2.3 (GND), J2.5 (GND), J2.9 (GNDDetect), PS1.2 (GND), PS1.4 (NC), S1.2, S1.3, U3.12 (VSSA), U3.18 (VSS), U3.31 (VSS), U3.47 (VSS), U3.63 (VSS); also elsewhere on the board
HEATER1_SWITCH_EN: U3.54 (PD2); also elsewhere on the board
HEATER2_SWITCH_EN: U3.40 (PC9); also elsewhere on the board
I2C1_SCL: R15.1, U3.58 (PB6); also elsewhere on the board
I2C1_SDA: R13.1, U3.59 (PB7); also elsewhere on the board
I2C2_SCL: R14.1, U3.29 (PB10); also elsewhere on the board
I2C2_SDA: R16.1, U3.30 (PB11); also elsewhere on the board
NRST: C27.2, S1.1, U3.7 (NRST)
unnamed: C23.1, C24.1
unnamed: J1.2, R12.1
unnamed: C41.2, C42.2, FB2.1, PS1.5 (OUT)
RCC_OSC_IN: C23.2, R11.1, U3.5 (PD0), Y1.2
RCC_OSC_OUT: C24.2, R11.2, U3.6 (PD1), Y1.1
SYS_JTDI: J2.8 (NC/TDI), U3.50 (PA15)
SYS_JTDO-TRACESWO: J2.6 (SWO/TDO), U3.55 (PB3)
SYS_JTICK-SWCLK: J2.4 (SWCLK/TCK), U3.49 (PA14)
SYS_JTMS-SWDIO: J2.2 (SWDIO/TMS), U3.46 (PA13)
SYS_NJTRST: J2.10 (~RESET)
VCC_BALANCE: C39.2, C40.2, PS1.1 (IN), PS1.3 (EN); also elsewhere on the board
Vbalance_sense_alert: U3.53 (PC12); also elsewhere on the board
Vbat_sense_alert: U3.27 (PB1); also elsewhere on the board

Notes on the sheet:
i2c1->chargers i2c2->current sense
LDO
VDDA pin decoupling caps+ 600ohm@100MHz(0.5A)
